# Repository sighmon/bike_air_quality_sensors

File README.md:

# Bike air quality sensors

A set of Carbon Monoxide & dust particle sensors combined with humidity/temperature sensors for measuring the air quality while cycling.

The sensors are hooked up to an Arduino which then sends the data via serial over Bluetooth to our Android or iOS phone to be time stamped and have GPS data added.

This data will then be sent to a Rails server to graph the data - and also provide an API for others to interact with it.

by Damien & Simon

## Hardware

* [Redbear Duo](https://github.com/redbear/Duo)
* [MQ-7 Carbon Monoxide sensor](https://www.sparkfun.com/products/9403)
* [GP2Y10 Dust Particle sensor](https://www.sparkfun.com/products/9689)
* [DHT-22 Temperature/Humidity sensor](https://www.sparkfun.com/products/10167)
* P-channel MOSFET
* 10K ohm resistor
* 20K ohm resistor
* 150 ohm resistor
* 220µF capacitor

## Output

The sensors are read every second and output in a struct:

`struct SENSOR_READINGS {
    float temperature;
    float humidity;
    float particles;
    float co;
    char heaterOn;
};`

* Temperature in Celsius
* Humidity %
* Dust particle raw sensor value
* Carbon monoxide raw sensor value
* Heater on/off sent as 1 or 0

### Power usage

* When heating the Carbon Monoxide sensor: 200 mA
* When not heating the Carbon Monoxide sensor: 130 mA

### Data from the iOS app with GPS location & timestamp

Google Spreadsheet: [bike sensor data](https://docs.google.com/spreadsheets/d/1QTtR4N6sVxgsv6Za4kGe6Mn_MdasWhGjeMLYdR82Do4/edit?usp=sharing)

[Interactive graph of the data](https://docs.google.com/spreadsheets/d/1QTtR4N6sVxgsv6Za4kGe6Mn_MdasWhGjeMLYdR82Do4/pubchart?oid=1328642199&amp;format=interactive)

## Libraries

Thanks for the DHT sensor library:
<https://learn.adafruit.com/dht/using-a-dhtxx-sensor>

Thanks for the Sharp Optical Dust Sensor library:
<http://arduinodev.woofex.net/2012/12/01/standalone-sharp-dust-sensor/>

MQ-7 Carbon Monoxide sensor:
<http://thesis.jmsaavedra.com/make/>

## iOS & Android apps

[iOS app](https://github.com/sighmon/BikeAirQualitySensorsiOS)

[Android app](https://github.com/33d/bike-air-sensor-logger)

Both apps add:

* ISO 8601 formatted time, including the time zone.
* The position - latitude and longitude.

Then they export the data to a CSV file.

## Python data parser for the CSV

The Carbon Monoxide sensor can only be read after it's been heating for 60 seconds, so we need to throw away all of the data around this.

This Python parser does just that. :-)

<https://github.com/sighmon/bike_air_quality_sensor_csv_parser>

## Manufactured by OSH Park

I got the first batch of boards manufactured by <https://oshpark.com>. You can see the shared project here: <https://oshpark.com/profiles/sighmon>

## GovHack Machinery of Data entry video

<iframe width="100%" height="315" src="https://www.youtube.com/embed/KiIhrwRlb6w" frameborder="0" allowfullscreen></iframe>

## Troubleshooting

- If the RedBear Duo gets itself into a flashing blue light of doom, hold down both ```reset + setup``` for 3 seconds, then let go of the reset. Hold the setup button until the flashing turns yellow. That’s DFU mode to [re-upload the user firmware](https://github.com/redbear/Duo/blob/master/docs/firmware_deployment_guide.md).

``` $ dfu-util -d 2b04:d058 -a 0 -s 0x80C0000 -D duo-user-part.bin```

## TODO

* <s>Connect sensors to the Arduino.</s>
* <s>Send data via Bluetooth.</s>
* <s>Build an iOS app.</s>
* <s>Build an Android app.</s>
* Build a Rails server to open up the data via a public API.

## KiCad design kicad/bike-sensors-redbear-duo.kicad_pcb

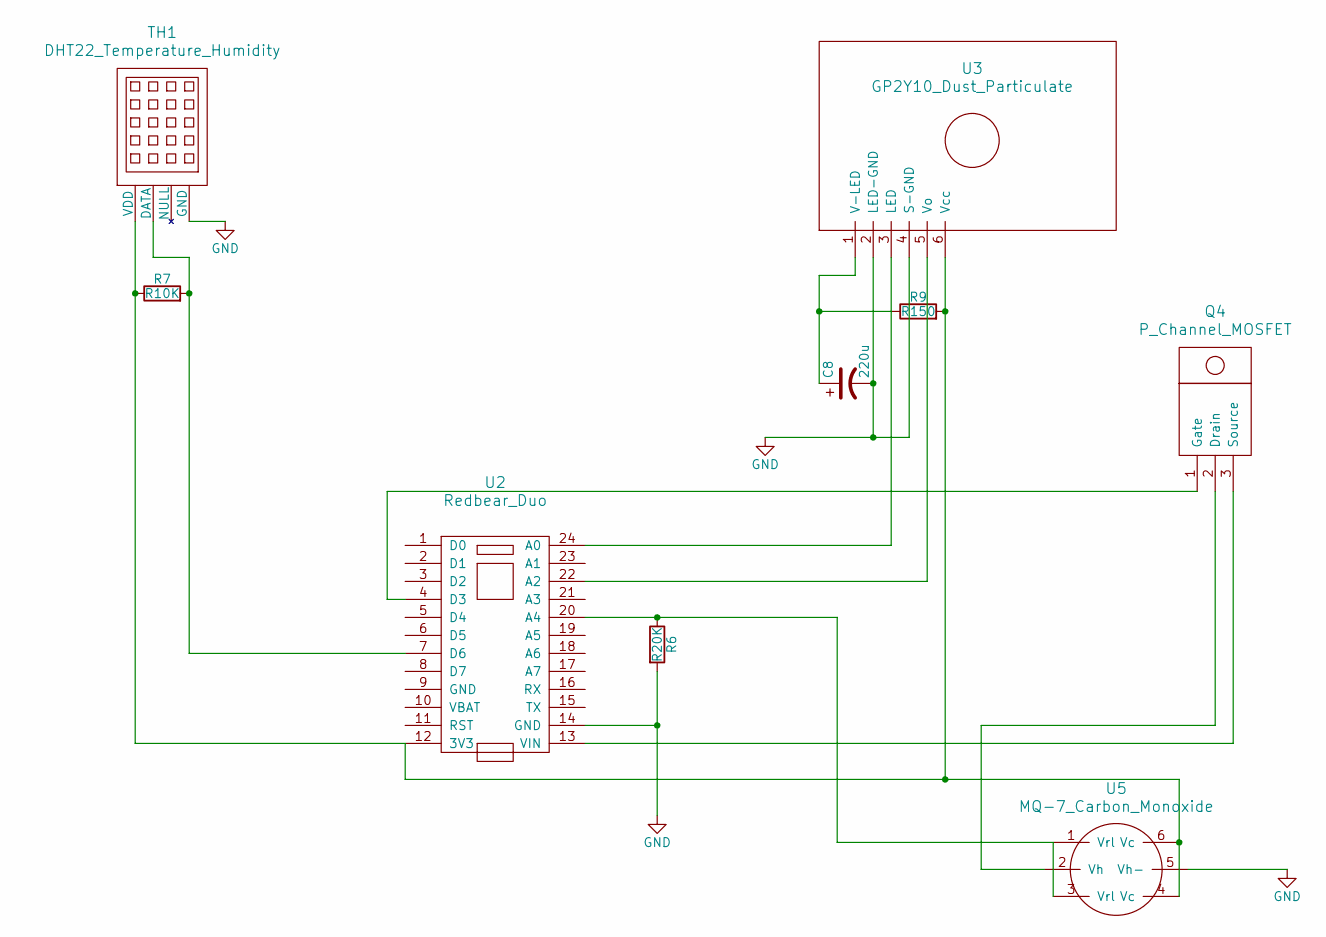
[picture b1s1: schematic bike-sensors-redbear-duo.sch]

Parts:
C8: 220u
Q4: P_Channel_MOSFET
R6: R20K
R7: R10K
R9: R150
TH1: DHT22_Temperature_Humidity
U2: Redbear_Duo
U3: GP2Y10_Dust_Particulate
U5: MQ-7_Carbon_Monoxide

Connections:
GND: C8.2, R6.2, TH1.4 (GND), U2.14 (GND), U3.2 (LED-GND), U3.4 (S-GND), U5.5 (Vh-)
unnamed: C8.1, R9.1, U3.1 (V-LED)
unnamed: Q4.1 (Gate), U2.4 (D3)
unnamed: Q4.2 (Drain), U5.2 (Vh)
unnamed: Q4.3 (Source), U2.13 (VIN)
unnamed: R6.1, U2.20 (A4), U5.1 (Vrl), U5.3 (Vrl)
unnamed: R7.1, R9.2, TH1.1 (VDD), U2.12 (3V3), U3.6 (Vcc), U5.4 (Vc), U5.6 (Vc)
unnamed: R7.2, TH1.2 (DATA), U2.7 (D6)
unnamed: U2.22 (A2), U3.5 (Vo)
unnamed: U2.24 (A0), U3.3 (LED)

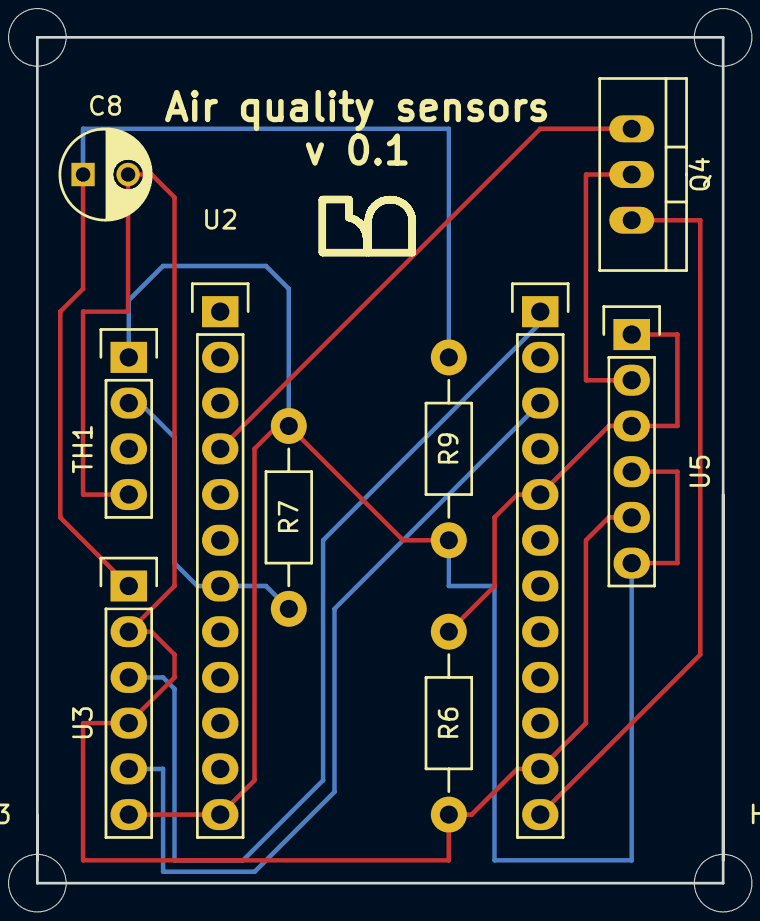
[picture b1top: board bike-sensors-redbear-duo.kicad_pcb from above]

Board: 2 copper layers, 38.1 x 47.0 mm, 13 parts (0 on the bottom side), 10 nets.

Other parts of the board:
HOLE1, HOLE2, HOLE3, HOLE4: MountingHole_3.2mm_M3

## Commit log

2015-09-19 First tests with the Humidity/Temperature sensor and Dust Particle sensor.
2015-09-23 Added MQ7 wiring pins.
2015-09-26 Added MQ-7 carbon monoxide sensor reading.
2015-09-26 Added TaskScheduler and moved reading sensors to functions.
2015-09-26 Added link to TaskScheduler
2015-09-26 Updated the README.
2015-10-03 Added CRC to the sensor reading lines. Only reading the sensors every 5 seconds now so the humidity and temperature sensor doesnt complain.
2015-10-03 Sensor prints a capital C when the CO heater is on, and a lowercase c when the heater is off. The reading is only meant to be accurate once the heater is off, but we need to test that.
2015-10-05 Added link to iOS app.
2015-10-07 Outputting sensor data as a struct to fit within 20 byte limit of BLE.
2015-10-14 Updated README to describe the output of sensor data in a struct.
2015-10-17 Added debugging output which can be uncommented so that data is readable by humans.
2015-10-24 Added link to the Python parser and Android app.
2015-10-31 Updated readme with GovHack MoD video entry link.
2015-10-31 Added images.
2015-10-31 Added images to README.
2016-04-02 Added Fritzing wiring diagrams.
2016-04-02 Rewrote TaskScheduler for Arm chipset so it compiles for the RedBear Duo.
2016-04-02 Getting it compiling on the RedBear Duo board.
2016-04-20 Added BLE setup for talking serial to iOS from the Redbear Duo.
2016-04-30 Now sending sensor data via BLE. Only sending every 80 bytes instead of 20 bytes.
2016-04-30 Trying to work with an ARM compatible DHT22 library: https://github.com/RobTillaart/Arduino/tree/master/libraries/DHTstable
2016-05-25 Doing the sensor readings in SINGLE_THREADED_BLOCK() so that they don't break the ble.
2016-05-28 The input from the RedBear Duo is 0-4096, so mapping that read value to 0-1024.
2016-06-04 Hooked up the optical dust sensor to D8 for LED power and A2 for the reading.
2016-06-04 Removed old DHT library defines.
2016-06-04 RGB LED on the RedBear Duo now turns red when the CO sensor is heating, and green when it's off.
2016-06-04 Blue LED on the RedBear Duo now lights up when a bluetooth device is connected. Added Battery reading, but not sure how to get that reading on the iOS side yet.
2016-06-15 Added some more debug information, and now reading every 2 seconds.
2016-06-15 Added Redbear Duo image.
2016-06-25 KiCad pcb files added
2016-07-23 Continued work on the schematic and starting to understand how the footprint works.
2016-07-27 Fixed the footprint. The magic was to append my custom RedbearDuo library to the Footprint Libraries Manager.
2016-08-13 Fixed the resistor junctions.
2016-08-20 Added text to silk screen layer, and simple Hackerspace logo.
2016-10-12 Manually routed tracks.
2016-10-12 Fixed the board edge on the bottom. Sent v0.1 off for manufacturing
2016-10-12 Added manufacturing information and v0.1 board image.
2016-10-12 Fixed image link.
2016-11-12 Added Gerber files generated and image of the manufactured board.
2016-11-13 Updated the parts list to include resistors and capacitor.
2017-01-07 Added enclosure freecad files.
2017-01-11 Removed support flange.
2017-01-11 Shortened USB cable gaps.
2017-01-14 Added enclosure top, and updated power usage.
2017-01-14 Added holes and aligning pins.
2017-01-18 Finished top enclosure.
2017-01-28 Added instructions to avoid flashing blue light of death.
2017-01-28 Added a dust straw to avoid dust getting on the boards.
2017-02-04 Added a blended straw option.
2017-02-15 Finished blended straw.
2017-02-15 Updated dimensions.
